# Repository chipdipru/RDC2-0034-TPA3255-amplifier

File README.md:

<p>Проект на - <a href="https://easyeda.com/Dmitry-Chernikov/Class-D-Audio-Amplifier-on-TPA3255-Chip" class="link">easyeda.com</a>.</p>

<p></p>

<p>Модуль RDC2-0034 представляет собой высокопроизводительный усилитель мощности класса D, который совмещает истинное качество звука премиум-класса с высоким КПД класса D.<br>Усилитель построен на микросхеме TPA3255. Это стереофонический аналоговый чип с цифровым усилителем Power Stage, предназначенный для работы с 4-омными громкоговорителями мощностью до 300 Вт на канал. Он имеет усовершенствованную интегрированную конструкцию обратной связи и исправление ошибок драйвера высокоскоростного шлюза (PurePath ™ Ultra-HD). Эта технология обеспечивает сверхнизкие искажения в звуковом диапазоне и превосходное качество звука.<br>RDC2-0034 сконфигурирован для работы с двумя каналами включенными по мостовой схеме (BTL).<br/>
 На аналоговый вход усилителя можно подавать как несимметричный так и симметричный (дифференциальный) сигнал.<br/>
 При необходимости два мостовых канала BTL можно включить параллельно, объединив их в один канал PBTL. При этом выходная мощность усилителя достигнет 600Вт.<br>Для обеспечения высококачественного высокоэффективного усиления звука требуется простой пассивный фильтр демодуляции цифрового сигнала. Модуль LCF.<br>Для питания схем управления и обработки сигнала усилителю требуется дополнительные источники питания – 12В и 3,3В. Модуль RDC1-0013 сформирует 15В из напряжения питания выходного каскада, а параметрические преобразователи на главной плате отдадут требуемые 12В и 3,3В.</p>
<h2>Технические характеристики</h2>
<p>Напряжение питания выходного каскада: 18-50 В<br>Количество каналов: 2 x BTL, 1 x PBTL<br>Сопротивление нагрузки: BTL 4-8 Ом<br>Сопротивление нагрузки: PBTL 2-3 Ом<br>Выходная мощность: BTL 318 Вт / 4 Ом 10% THD или 180 Вт / 8 Ом / 10% THD<br>Выходная мощность PBTL 607 Вт / 2 Ом / 10% THD<br>Выходная мощность: BTL 260 Вт / 4 Ом 1% THD или 150 Вт / 8 Ом / 1% THD<br>Выходная мощность: PBTL 480 Вт / 2 Ом / 1% THD<br>Коэффициент нелинейных искажений:0.006%<br>КПД с нагрузкой 4Ом: 90%</p>
<p>Схема основной платы усилителя.</p>
<p></p>
<p>Подробную инструкцию по включению и конфигурации усилителя можно найти в разделе «Документы».</p>
<p>Это открытый проект! Лицензия, под которой он распространяется – <a href="https://creativecommons.org/licenses/by-sa/3.0/" class="link">Creative Commons - Attribution - Share Alike license</a>.</p>

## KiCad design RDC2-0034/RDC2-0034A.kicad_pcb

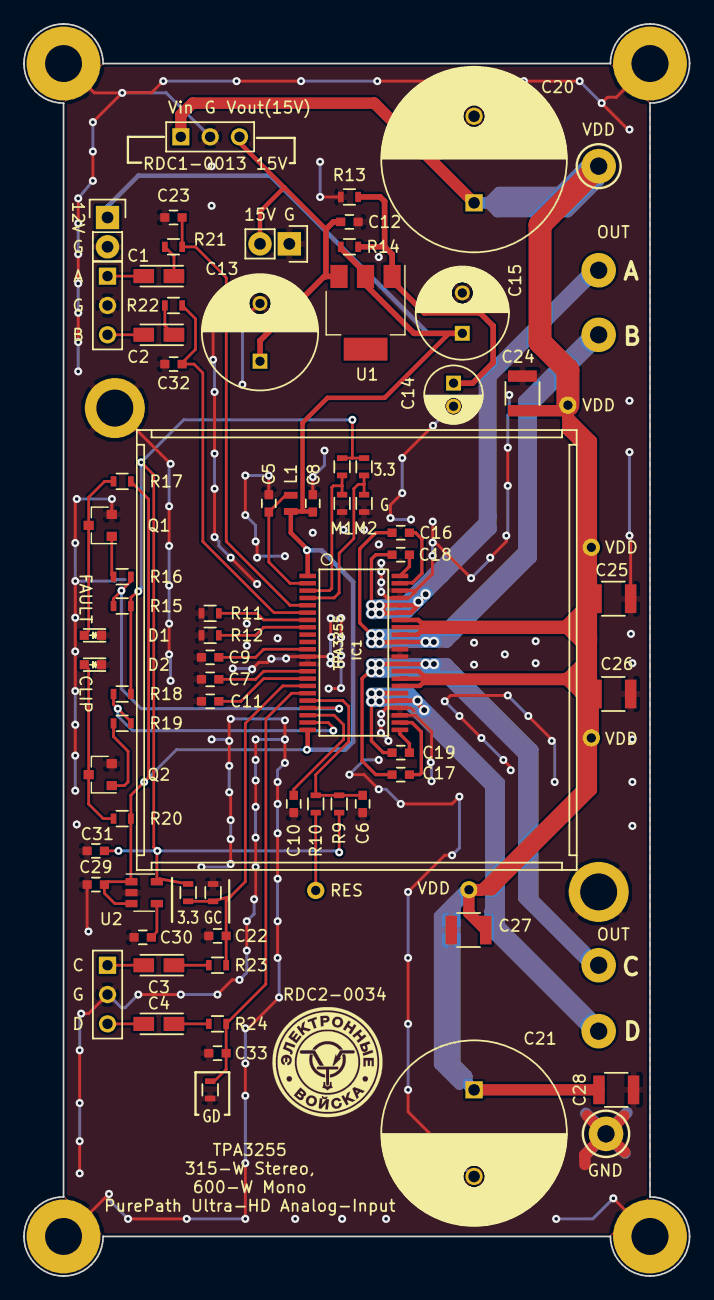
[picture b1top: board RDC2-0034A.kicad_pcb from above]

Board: 2 copper layers, 57.7 x 108.5 mm, 78 parts (0 on the bottom side), 44 nets.

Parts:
C1, C2, C3, C4: 10; TantalC_SizeA_EIA-3216_Reflow
C5, C10, C12: 0,1; C_0603
C6, C22, C23, C32, C33: 100; C_0603
C7, C9: 1 uF; C_0603
C8: C; C_0603
C11: 0,047 uF; C_0603
C13: 470 uF; C_Radial_D10_L13_P5
C14: 10 uF; C_Radial_D5_L11_P2
C15: 100 uF; C_Radial_D8_L11.5_P3.5
C16, C17, C18, C19: 0,033; C_0603
C20, C21: 1000 uF; C_Radial_D16_L25_P7.5
C24, C25, C26, C27, C28: 2,2; C_1210
C29: 1; C_0603
C30: 0,01; C_0603
C31: 4,7; C_0603
D1, D2: LED; LED_0603
IC1: TPA3255; TSSOP-44
L1: 10μH; Neosid_Inductor_SM0603CG
P1: InAB; Pin_Header_Straight_1x03_mm
P2: InCD; Pin_Header_Straight_1x03_mm
P3: CONN_01X03; Pin_Header_Straight_1x03_mm
P4, P5, P11, P12, P13, P14: CONN_01X01; Measurement_Point_Round-TH_Big
P6, P7, P8, P9, P10: CONN_01X01; Measurement_Point_Round-TH_Small
Q1, Q2: 2N7002; SOT-23
R1, R2, R4, R5, R6, R7, R8: R; R_0603
R9: 10K; R_0603
R10, R16, R19, R21, R22, R23, R24: 100; R_0603
R11: 22K; R_0603
R12: 30K; R_0603
R13: 4k7; R_0603
R14: 560R; R_0603
R15, R18: 47K; R_0603
R17, R20: 1K; R_0603
U1: LM317_SOT223; SOT-223
U2: LP2985L_3.3V; SOT-23-5

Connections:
12V: C8.1, C15.1, C29.2, IC1.1, IC1.22, L1.1, R14.2, R17.1, R20.1, U1.2, U2.1, U2.3
15V: C12.2, C13.1, P3.3, U1.3
+3V3: C31.2, R1.2, R5.2, R7.2, R9.1, R15.1, R18.1, U2.5
CLIP: IC1.21, R18.2, R19.1
FAULT: IC1.19, R15.2, R16.1
GND: C5.2, C6.2, C7.2, C8.2, C9.2, C10.2, C11.2, C12.1, C13.2, C14.2, C15.2, C20.2, C21.2, C22.2, C23.1, C24.1, C25.1, C26.1, C27.1, C28.1, C29.1, C30.1, C31.1, C32.1, C33.2, D1.1, D2.1, IC1.12, IC1.13, IC1.25, IC1.26, IC1.33, IC1.34, IC1.41, IC1.42, P1.2, P2.2, P3.2, P5.1, Q1.2, Q2.2, R2.2, R4.2, R6.1, R8.1, R11.1, R12.1, R13.1, U2.2
INC: C22.1, IC1.16, R1.1, R2.1, R23.2
IND: C33.1, IC1.17, R4.1, R24.2
unnamed: C1.1, R21.1
unnamed: C1.2, P1.1
unnamed: C2.1, R22.1
unnamed: C2.2, P1.3
unnamed: C3.1, R23.1
unnamed: C3.2, P2.1
unnamed: C4.1, R24.1
unnamed: C4.2, P2.3
unnamed: C5.1, IC1.2, L1.2
unnamed: C6.1, IC1.18, R9.2, R10.2
unnamed: C7.1, IC1.14
unnamed: C9.1, IC1.11
unnamed: C10.1, IC1.20
unnamed: C11.1, IC1.15
unnamed: C14.1, R13.2, R14.1, U1.1
unnamed: C16.1, IC1.35, P12.1
unnamed: C16.2, IC1.43
unnamed: C17.1, IC1.24
unnamed: C17.2, IC1.32, P13.1
unnamed: C18.1, IC1.39, IC1.40, P11.1
unnamed: C18.2, IC1.44
unnamed: C19.1, IC1.23
unnamed: C19.2, IC1.27, IC1.28, P14.1
unnamed: C23.2, IC1.5, R21.2
unnamed: C30.2, U2.4
unnamed: C32.2, IC1.6, R22.2
unnamed: D1.2, Q1.3, R17.2
unnamed: D2.2, Q2.3, R20.2
unnamed: IC1.3, R7.1, R8.2
unnamed: IC1.4, R5.1, R6.2
unnamed: IC1.7, R11.2
unnamed: IC1.8, R12.2
unnamed: Q1.1, R16.2
unnamed: Q2.1, R19.2
RES: P10.1, R10.1
VDD: C20.1, C21.1, C24.2, C25.2, C26.2, C27.2, C28.2, IC1.29, IC1.30, IC1.31, IC1.36, IC1.37, IC1.38, P3.1, P4.1, P6.1, P7.1, P8.1, P9.1

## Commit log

2018-09-20 KiCad project
2018-09-20 schematic
